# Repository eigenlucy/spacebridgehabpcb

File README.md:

# SpaceBridge HAB PCB

High Altitude Balloon (HAB) PCB Tracker with cutdown mechanism, GPS, environmental monitoring, LoRa telemetry and particle detection capabilities.

Created by Lucy Moglia <eigenlucy@proton.me>

## Table of Contents
- [Overview](#overview)
- [Project Structure](#project-structure)
- [Block Diagram](#block-diagram)
- [Features](#features)
- [Getting Started](#getting-started)
  - [Building the Project](#building-the-project)
  - [Installation](#installation)
    - [Linux Installation](#linux-installation)
    - [Mac Installation](#mac-installation)
    - [Visual Studio Code/Cursor Extension](#visual-studio-codecursor-extension-install)

## Overview

The SpaceBridge HAB PCB is a comprehensive tracking and instrumentation system for high altitude balloon experiments. It integrates multiple subsystems including power management, telemetry, GPS tracking, environmental monitoring, and a particle counter based on CERN open source hardware.

## Project Structure

| Module | Source File | PCB Layout | Description |
|:------:|:----------:|:----------:|:------------|
| Mainboard | [`mainboard.ato`](./mainboard.ato) | [`layouts/default/default.kicad_pcb`](./layouts/default/default.kicad_pcb) | Final PCB incorporating all submodules |
| MicroMPPT | [`micromppt/elec/src/micromppt.ato`](./micromppt/elec/src/micromppt.ato) | [`micromppt/elec/layout/default/micromppt.kicad_pcb`](./micromppt/elec/layout/default/micromppt.kicad_pcb) | 5W MPPT battery charger with embedded set point adjustment algorithm |
| Particle Counter | [`particle_counter.ato`](./particle_counter.ato) | [`layouts/particle-counter/particle-counter.kicad_pcb`](./layouts/particle-counter/particle-counter.kicad_pcb) | Alpha particle detector based on CERN open source hardware kit |
| Cutoff Mechanism | [`cutoff.ato`](./cutoff.ato) | [`layouts/cutoff/cutoff.kicad_pcb`](./layouts/cutoff/cutoff.kicad_pcb) | Balloon cutoff circuit using lithium hybrid supercapacitor discharging through nichrome wire |
| BQ24045DSQR BMS | [`bq24045dsqr/elec/src/bq24045dsqr.ato`](./bq24045dsqr/elec/src/bq24045dsqr.ato) | [`bq24045dsqr/elec/layout/default/bq24045dsqr.kicad_pcb`](./bq24045dsqr/elec/layout/default/bq24045dsqr.kicad_pcb) | 5V 1A single cell LiPo/Li-ion charger + BMS |
| TPS63020DSJR | `~/.ato/modules/tps63020dsjr/elec/src/tps63020dsjr.ato` | `~/.ato/modules/tps63020dsjr/elec/layout/tps63020dsjr.kicad_pcb` | 1.8V-5.5V In/Out 4A boost-buck converter (5V from Vbat) |

## Block Diagram

### Original Block Diagram

### Mermaid Diagram
```mermaid
graph TD
    %% Power System
    Solar["Solar Panel"] --> MPPT["SPV1040 MicroMPPT"]
    MPPT --> BattProt["UVP/OCP/OVP Battery Protection"]
    BattProt --- Battery["LTO Battery"]
    BattProt --> BoostBuck["TPS63020 Boost-Buck"]
    BoostBuck --> Power5V["5V Power Rail"]
    
    %% ESP32 Microcontroller (Central)
    ESP32["ESP32-S3"] 
    
    %% 5V Devices
    Power5V --> LoRa["E22-900M30S/SX1262 LoRa Module"]
    Power5V --> ParticleCounter["CERN DIY Particle Counter"]
    Power5V --> CutoffSystem["Cutoff System"]
    
    %% Cutoff System Components
    CutoffSystem --> Supercap["3.5V Low ESR Supercap"]
    CutoffSystem --> Nichrome["Nichrome Wire ~20Ω"]
    CutoffSystem --> TIP120["TIP120 NPN Darlington"]
    
    %% I2C Devices (3.3V)
    ESP32 -- I2C/IO6+IO7 --> OLED["SSD1306 128x32 OLED"]
    ESP32 -- I2C/IO6+IO7 --> BME680["BME680 Sensor"]
    ESP32 -- I2C/IO6+IO7 --> GPS["ATGM336H GNSS/GPS"]
    
    %% SPI Connections
    ESP32 -- SPI/IO10-13 --> LoRa
    
    %% GPIO Connections
    ESP32 -- GPIO0 --> Supercap["SC_GATE (Supercap Control)"]
    ESP32 -- GPIO1 --> TIP120["CUTOFF_GATE (Nichrome Control)"]
    
    %% ADC Connections
    ParticleCounter -- ADC/GPIO2 --> ESP32
    
    %% Antenna
    LoRa --- Antenna["915MHz LoRa Antenna (30dBm TX max)"]
    
    %% Styling
    classDef power fill:#f96,stroke:#333,stroke-width:2px
    classDef sensor fill:#bbf,stroke:#333,stroke-width:1px
    classDef communication fill:#f9f,stroke:#333,stroke-width:1px
    classDef controller fill:#9f6,stroke:#333,stroke-width:2px
    
    class Solar,MPPT,BattProt,Battery,BoostBuck,Power5V,Supercap power
    class BME680,ParticleCounter,GPS sensor
    class LoRa,Antenna,OLED communication
    class ESP32 controller
```

## Features

- **Power Management**: Solar charging with MPPT, battery protection and 5V regulation
- **Communication**: 915MHz LoRa radio for long-range telemetry (30dBm TX max)
- **Positioning**: ATGM336H GNSS/GPS module
- **Sensors**: 
  - BME680 temperature/humidity/pressure/gas sensor
  - CERN DIY particle counter for radiation detection
- **Display**: SSD1306 128x32 OLED screen
- **Control**: ESP32-S3 microcontroller
- **Recovery**: Nichrome wire cutdown mechanism for payload separation

## Getting Started

### Building the Project

1. **Clone the required submodules**
   ```
   git submodule update --init --recursive
   ```

2. **Build the project to select components based on JLCPCB availability**
   ```
   ato build -t all
   ```

3. **Complete/review the layout with KiCad Standalone PCB editor**

4. **Gerbers/PCBA files are generated through an Actions run on a commit**

### Installation

#### Linux Installation
1. Install [uv](https://github.com/astral-sh/uv)
2. Install KiCad with your preferred package manager (apt for Debian, pacman for Arch, etc.)
3. Install atopile as a tool with uv (Python 3.13.2 recommended):
   ```
   uv tool install atopile
   ```

   **Alternative installation method:**
   1. Clone the main [atopile repo](https://github.com/atopile/atopile)
   2. Remove the uv lock file:
      ```
      rm uv.lock
      ```
   3. Sync repo to dev release:
      ```
      uv sync --dev
      ```
   4. Compile atopile:
      ```
      uv build
      ```
   5. Install the binary:
      ```
      uv tool install atopile-0.3.XX-cp313-cp313-linux-_x86_64.whl
      ```
   6. Add the uv tools binary directory to your PATH (command depends on your shell, e.g., with fish):
      ```
      fish_add_path /home/user/.local/share/uv/tools/atopile/
      ```

4. Check your version:
   ```
   ato --version
   ```

5. Configure the atopile plugin:
   ```
   ato configure
   ```

#### Mac Installation
1. Install [Homebrew](https://brew.sh/)
2. Install [KiCad 9](https://formulae.brew.sh/cask/kicad):
   ```
   brew install --cask kicad
   ```
3. Install atopile with Homebrew:
   ```
   brew install atopile/tap/atopile
   ```
4. Configure the atopile plugin:
   ```
   ato configure
   ```

#### Visual Studio Code/Cursor Extension Install
Install the [atopile extension](https://marketplace.visualstudio.com/items?itemName=atopile.atopile) into Cursor or Visual Studio Code.

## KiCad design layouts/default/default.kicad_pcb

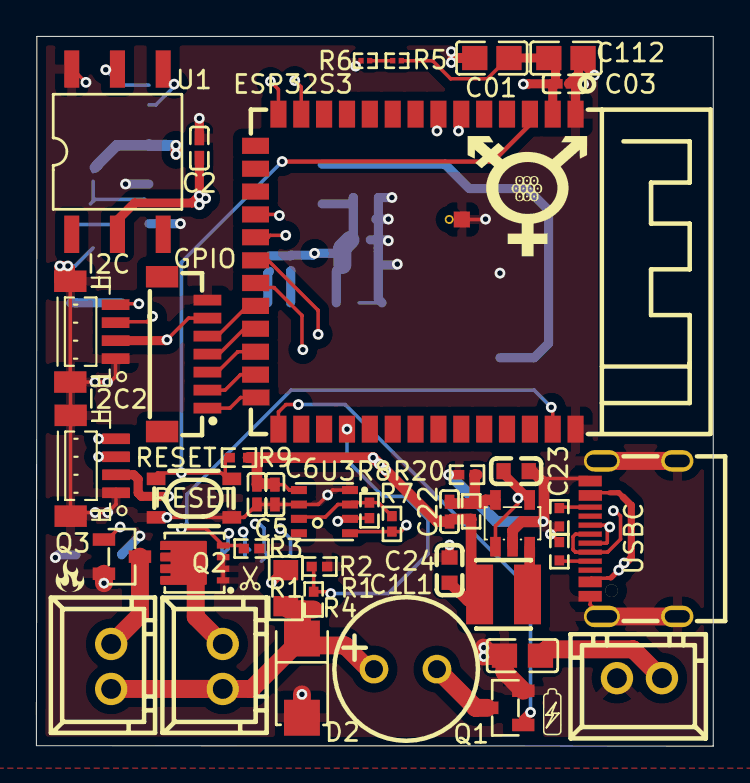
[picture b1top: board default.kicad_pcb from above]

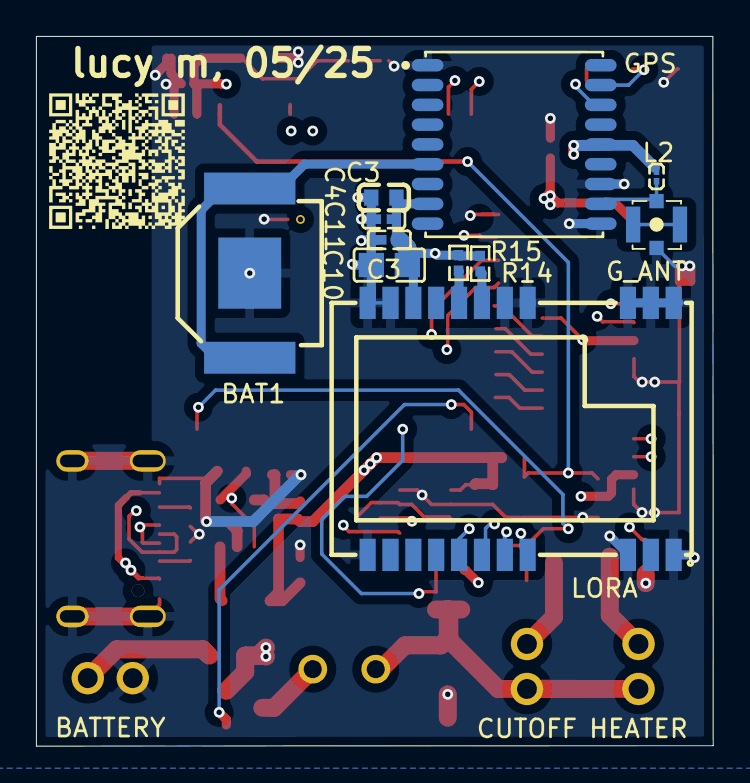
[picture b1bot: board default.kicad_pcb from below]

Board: 4 copper layers, 37.6 x 39.4 mm, 52 parts (11 on the bottom side), 36 nets.

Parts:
BAT1: BAT-SMD_C238096-012a28
BATTERY: CONN-TH_XH-2A-b4a6f6
C01, C112: 10µF ±10% 25V X5R; C0805-3b2e55
C1: CAP-TH_BD8.0-P3.50-D0.6-FD_1-b17e9d
C2, C03, C4, C5, C6, C11, C22: 100nF ±10% 16V X7R; C0402-b3ef17
C3, C23, C24: 100nF ±10% 50V X7R; C0603-bd72f6
C10, C30: 100nF ±10% 50V X7R; C0805-3b2e55
CUTOFF: CONN-TH_XH-2A-b4a6f6
D2: SMA_L4.3-W2.6-LS5.2-RD-e14692
ESP32S3: WIRELM-SMD_ESP32-S3-WROOM-1
GPIO: CONN-SMD_7P-P1.00_BM07B-SRSS-TB-201aba
GPS: GPSM-SMD_ATGM336H-TR-d79f58
G_ANT: IPEX-SMD_4P-L2.6-W2.6-LS3.0-f1620f
HEATER: CONN-TH_XH-2A-b4a6f6
I2C, I2C2: CONN-SMD_BM04B-SRSS-TB-6963ef
L1: IND-SMD_L3.0-W3.0-a13401
L2: L0201-8d2bbc
LORA: WIRELM-SMD_E22-900M22S-72e54e
Q1, Q3: SOT-23-3_L2.9-W1.3-P1.90-LS2.4-BR-688f29
Q2: DFN-8_L3.3-W3.3-P0.65-BL-2-bd6bc9
R1: 10kΩ ±1% 125mW; R0805-c79e8b
R2, R3, R4, R7, R8, R9, R14, R15: 10kΩ ±1% 62.5mW; R0402-56259e
R5: 10kΩ ±1% 50mW; R0201-27027e
R6: R0201-27027e
R20: 200kΩ ±1% 62.5mW; R0402-56259e
R21: 887kΩ ±1% 62.5mW; R0402-56259e
RESET: KEY-SMD_4P-L4.2-W3.2-P2.20-LS4.6
U1: SOP-6_L7.0-W7.0-P2.54-LS10.3-BL-0df1ed
U3: LGA-8_L3.0-W3.0-P0.80_BME688-7465bb
U19, U29: 5.1kΩ ±1% 62.5mW; R0402-56259e
U26: SOT-23-5_L3.0-W1.7-P0.95-LS2.8-BR-9d80aa
USBC: USB-C-SMD_KH-TYPE-C-16P

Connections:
A5: U19.1, USBC.A5
CC2: U29.1, USBC.B5
CSB: R7.2, R8.2, U3.2, U3.6
CUTOFF_GATE: ESP32S3.39, Q2.4, R3.1
FB: C22.2, R20.1, R21.2, U26.5
K: C1.1, CUTOFF.1, D2.1, HEATER.1, R1.2, R4.1
MISO: ESP32S3.21, LORA.16
MNT: G_ANT.1, G_ANT.3
MOSI: ESP32S3.19, LORA.17
NSS: ESP32S3.18, LORA.19
RF_IN: GPS.11, G_ANT.4, L2.2
RXEN: LORA.6, R14.2
Reserved: GPS.15, GPS.18
SCK: ESP32S3.20, LORA.18
SCL: ESP32S3.6, GPS.17, I2C.4, I2C2.4, R7.1, U1.5, U3.4
SC_GATE: ESP32S3.27, Q1.1
SC_Sense: ESP32S3.30, R2.1, R4.2
SDA: ESP32S3.7, GPS.16, I2C.3, I2C2.3, R8.1, U1.4, U3.3
SW: L1.1, U26.3
TEMP: R5.2, R6.1
TXEN: LORA.7, R15.2
VBAT: BAT1.1, BAT1.2, GPS.6
cutoff-C: CUTOFF.2, Q2.5
cutoff-C-1: HEATER.2, Q3.3
cutoff-C-2: C1.2, Q1.3
gnd: BAT1.3, BATTERY.2, C01.2, C2.2, C03.2, C3.2, C4.2, C5.2, C6.2, C10.2, C11.2, C23.2, C24.2, C30.2, C112.2, D2.2, ESP32S3.1, ESP32S3.40, ESP32S3.41, GPIO.7, GPS.1, GPS.10, GPS.12, G_ANT.2, I2C.0, I2C.1, I2C2.0, I2C2.1, LORA.1, LORA.2, LORA.3, LORA.4, LORA.5, LORA.10, LORA.11, LORA.12, LORA.20, LORA.22, Q1.2, Q2.1, Q2.2, Q2.3, Q3.2, R2.2, R3.2, R6.2, R20.2, RESET.3, RESET.4, U1.6, U3.1, U3.7, U19.2, U26.2, U29.2, USBC.1, USBC.2, USBC.3, USBC.4, USBC.A1, USBC.A12, USBC.B1, USBC.B12
hv: BATTERY.1, C23.1, C30.1, R1.1, U26.1, U26.4, USBC.A4, USBC.A9, USBC.B4, USBC.B9
hv-1: C01.1, C2.1, C03.1, C3.1, C4.1, C5.1, C6.1, C10.1, C11.1, C22.1, C24.1, C112.1, ESP32S3.2, GPIO.6, GPS.8, GPS.14, I2C.2, I2C2.2, L1.2, L2.1, LORA.9, R5.1, R9.1, R14.1, R15.1, R21.1, U1.2, U3.8
input: R9.2, RESET.1, RESET.2
io14: ESP32S3.22, GPIO.5
io19: ESP32S3.13, USBC.A7, USBC.B7
io20: ESP32S3.14, USBC.A6, USBC.B6
io21: ESP32S3.23, GPIO.4
io45: ESP32S3.26, GPIO.1
io47: ESP32S3.24, GPIO.3
io48: ESP32S3.25, GPIO.2

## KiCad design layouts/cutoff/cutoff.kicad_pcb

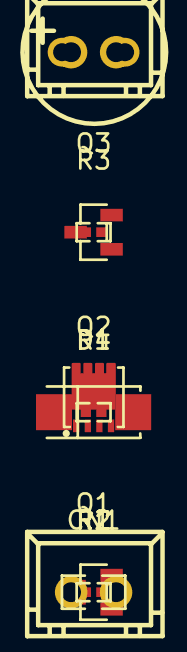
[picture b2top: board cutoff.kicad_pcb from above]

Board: 2 copper layers, 11 parts (0 on the bottom side), 7 nets, no tracks yet.

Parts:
C1: CAP-TH_BD8.0-P3.50-D0.6-FD_1-b17e9d
CN1, CN2: CONN-TH_XH-2A-b4a6f6
D1: SMA_L4.3-W2.6-LS5.2-RD-e14692
Q1, Q3: SOT-23-3_L2.9-W1.3-P1.90-LS2.4-BR-688f29
Q2: DFN-8_L3.3-W3.3-P0.65-BL-2-bd6bc9
R1: 10kΩ ±1% 125mW; R0805-c79e8b
R2, R3, R4: 10kΩ ±1% 62.5mW; R0402-56259e

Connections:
C: C1.2, Q1.3
C-1: CN1.2, Q2.5
C-2: CN2.2, Q3.3
CUTOFF_GATE: Q2.4, R3.1
K: C1.1, CN1.1, CN2.1, D1.1, R1.2, R4.1
SC_Sense: R2.1, R4.2
gnd: D1.2, Q1.2, Q2.1, Q2.2, Q2.3, Q3.2, R2.2, R3.2

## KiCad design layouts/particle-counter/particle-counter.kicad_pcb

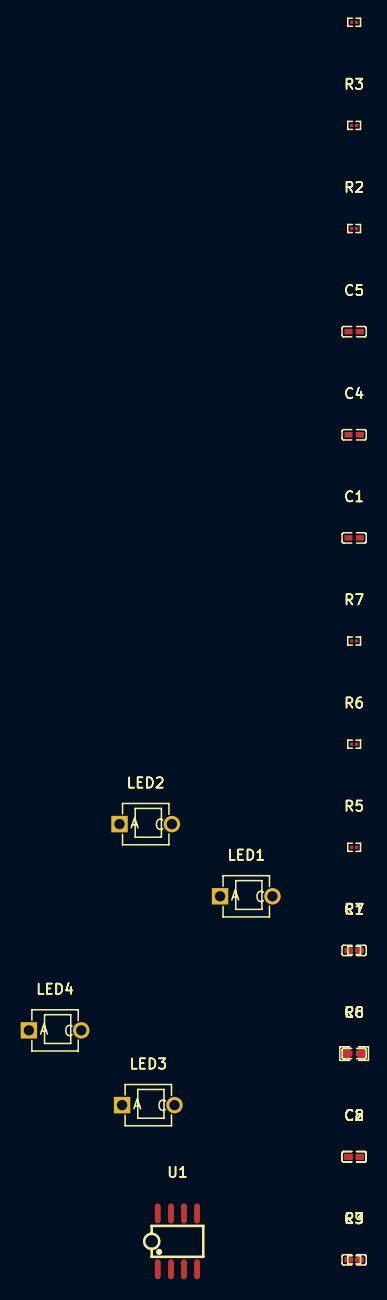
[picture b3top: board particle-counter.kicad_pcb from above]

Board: 2 copper layers, 22 parts (0 on the bottom side), 11 nets, no tracks yet.

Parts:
C1, C2, C3, C4, C5, C6, C7, C8: 100nF ±10% 16V X7R; C0402-b3ef17
LED1, LED2, LED3, LED4: SENSOR-TH_BPW34-c0a4b0
R1, R2, R3, R4, R5, R6, R7, R9: 1kΩ ±1% 50mW; R0201-27027e
R8: 10kΩ ±1% 100mW; R0603-ebcab9
U1: SOIC-8_L5.0-W4.0-P1.27-LS6.0-BL-294f77

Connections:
IN1plus: R1.2, R2.1, U1.3
IN2minus: C5.1, R4.2, R5.1, U1.6
IN2plus: C6.1, R6.2, R7.1, U1.5
K: C1.1, LED1.2, LED2.2, LED3.2, LED4.2, R3.1, U1.2
OUT1: C1.2, C3.1, R3.2, U1.1
OUT2: C5.2, R5.2, R8.1, U1.7
VCC: C4.1, R1.1, R6.1, U1.8
gnd: C4.2, C6.2, C7.2, LED1.1, LED2.1, LED3.1, LED4.1, R2.2, R7.2, R9.2, U1.4
net: C7.1, C8.1, R8.2
net-1: C3.2, R4.1
out: C8.2, R9.1

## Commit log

2025-04-07 intial commit
2025-04-08 added sensors, darlington transistor
2025-04-08 added particle counter repo for reference, added micromppt, added block diagram in /references
2025-04-08 clean up
2025-04-08 finished particle counter connections
2025-04-08 changed main target to mainboard, added cutoff build, lots of edits to modules
2025-04-08 finished cutoff mechanism connections
2025-04-08 finished cutoff mechanism connections :fixed
2025-04-08 new readme
2025-04-08 added zener to cutoff
2025-04-08 updated instructions
2025-04-08 fixed cutoff zener name
2025-04-09 added bme688
2025-04-09 fixed lora module and bme688
2025-04-11 major updates
2025-04-11 added boost buck
2025-04-11 readme format
2025-04-12 pcb layout
2025-04-13 save
2025-04-13 readme
2025-04-13 mermaid diagram
2025-04-30 built
2025-04-30 layout updates
2025-04-30 added new oled
2025-05-01 changed layout
2025-05-05 update before removing oled
2025-05-07 desktop push
2025-05-15 im cooking
2025-06-02 ordered
2025-06-14 added ntc connection
2025-06-23 firmware updates
2025-07-07 edits
